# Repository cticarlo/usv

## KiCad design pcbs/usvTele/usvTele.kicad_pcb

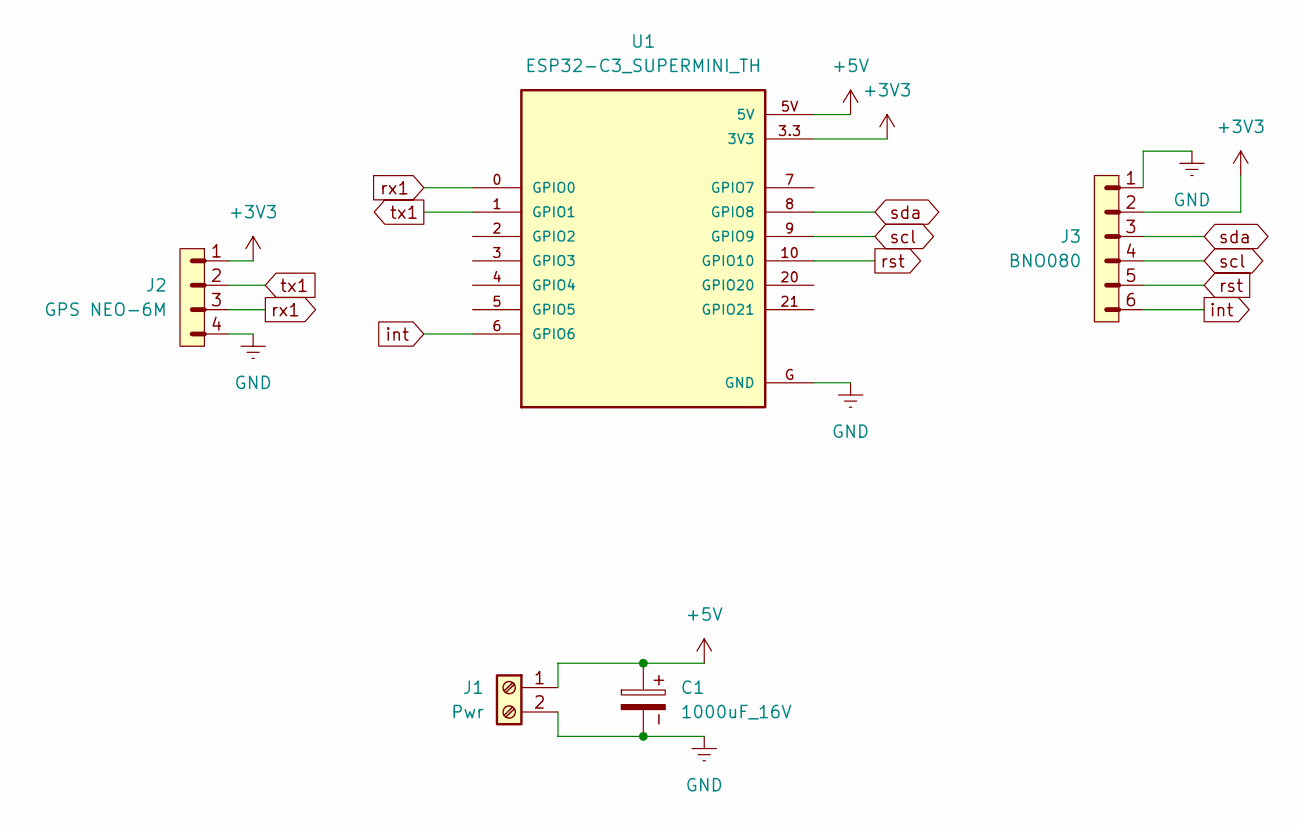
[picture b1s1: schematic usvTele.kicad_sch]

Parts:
C1: 1000uF_16V; CP_Radial_D8.0mm_P3.80mm
J1: Pwr; TerminalBlock_MetzConnect_Type101_RT01602HBWC_1x02_P5.08mm_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
J2: GPS NEO-6M; PinHeader_1x04_P2.54mm_Vertical
J3: BNO080; PinHeader_1x06_P2.54mm_Vertical
U1: ESP32-C3_SUPERMINI_TH; MODULE_ESP32-C3_SUPERMINI

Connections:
+3V3: J2.1, J3.2, U1.3.3 (3V3)
+5V: C1.1, J1.1, U1.5V
GND: C1.2, J1.2, J2.4, J3.1, U1.G (GND)
int: J3.6, U1.6 (GPIO6)
rst: J3.5, U1.10 (GPIO10)
rx1: J2.3, U1.0 (GPIO0)
scl: J3.4, U1.9 (GPIO9)
sda: J3.3, U1.8 (GPIO8)
tx1: J2.2, U1.1 (GPIO1)

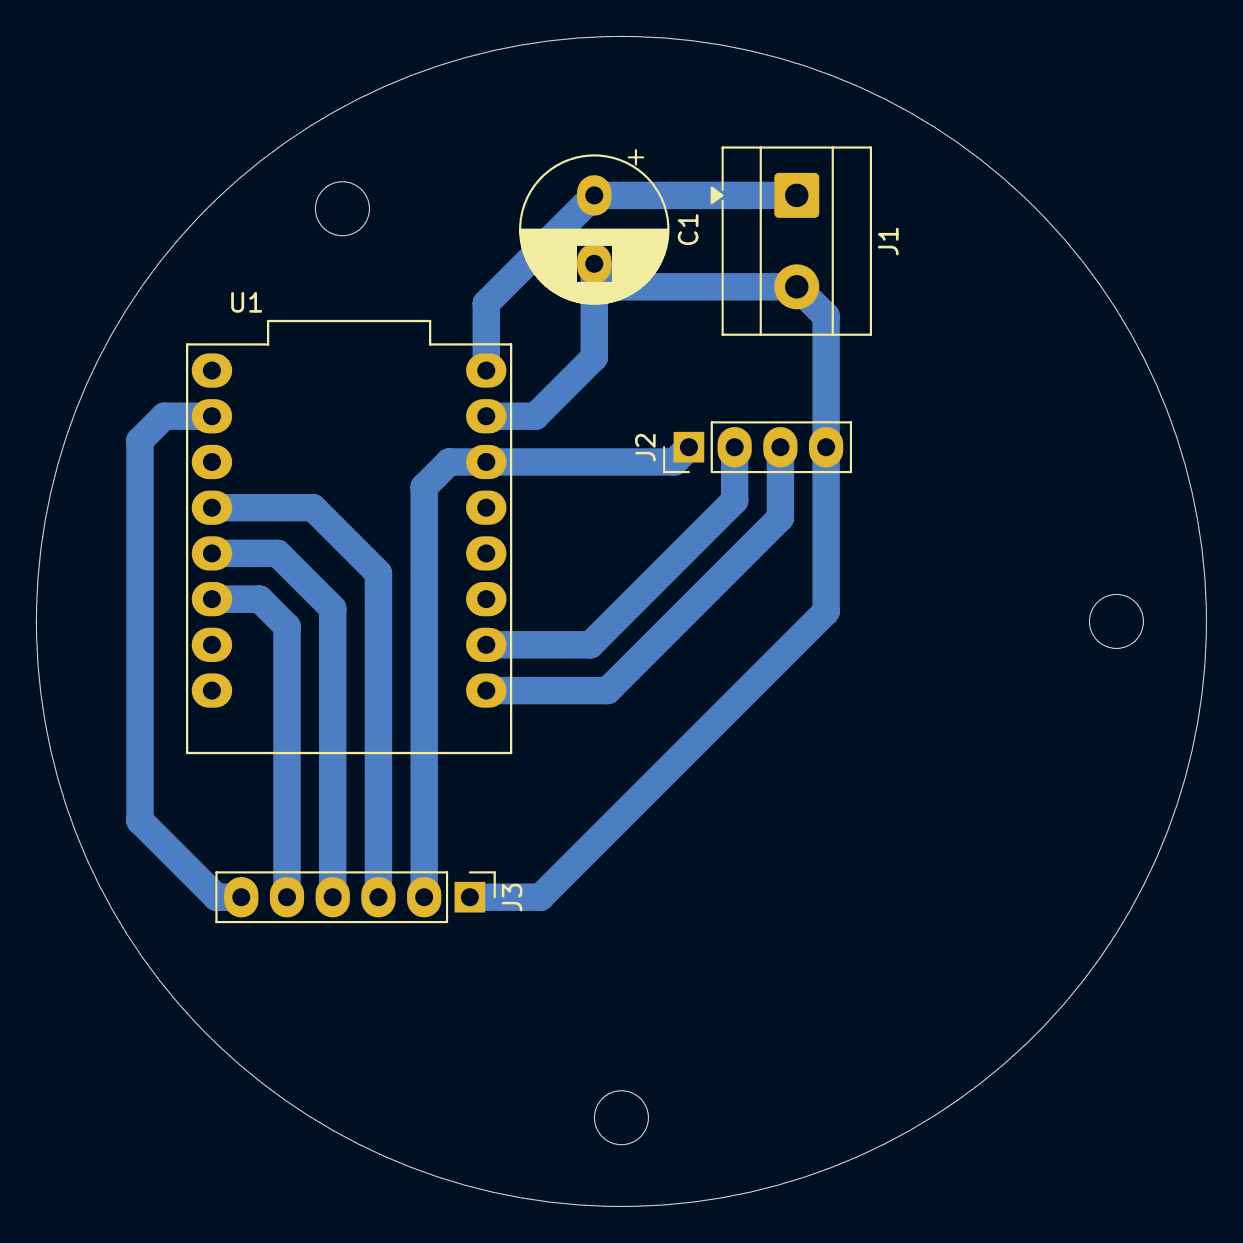
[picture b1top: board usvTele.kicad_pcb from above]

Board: 2 copper layers, 65.0 x 65.0 mm, 5 parts (0 on the bottom side), 9 nets.
